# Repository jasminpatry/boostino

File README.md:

# BooSTIno
A Teensy 3.6-based logger and gauge for my 2014 Subaru STI.

Photo of current version:

Short [YouTube video](https://www.youtube.com/watch?v=nscQxxUsuL8) of older version, without faceplate or wideband support:

See [this thread on NASIOC](https://forums.nasioc.com/forums/showthread.php?t=2896098) for more info.

# Compilation

This project is built as an Arduino sketch. I used Arduino 1.8.8, but later versions will likely work too. You will also need the Teensyduino add-on
(https://www.pjrc.com/teensy/td_download.html), and the following libraries:

* My fork of ILI9341_t3: https://github.com/jasminpatry/ILI9341_t3
* My fork of Adafruit_GFX: https://github.com/jasminpatry/Adafruit-GFX-Library
* font_Exo-BoldItalic: https://github.com/FrankBoesing/fonts/tree/master/ofl/exo

# Hardware

This project was built using the following hardware:

* [Teensy 3.6](https://www.pjrc.com/store/teensy36.html)
* MC33660 K-line serial interface chip, SOP-8 package ([datasheet](https://www.nxp.com/docs/en/data-sheet/MC33660.pdf)); I purchased mine from [eBay](https://www.ebay.com/itm/10PCS-MC33660-MC33660EF-SOP-8/292559702234)
* Custom PCB fabricated using the files in the [KiCad/boostino.gerber](KiCad/boostino.gerber) directory (I used [BasicPCB](https://www.basicpcb.com/)'s ValueSpec option, which in 2020 cost me about $30 for 3 boards).
* [HiLetgo ILI9341 2.8" SPI TFT LCD Display Touch Panel 240X320 with PCB 5V/3.3V STM32](https://www.amazon.com/gp/product/B073R7BH1B/)
* [OBD-2 cable](https://www.amazon.com/gp/product/B01ETRINYO/) &mdash; the switch and DB9 connector in the linked cable aren't necessary (I snipped them off), but the DB9 connector was useful when prototyping.
* [Innovate Motorsports (3877) LC-2 Digital Wideband Lambda Controller Kit with Bosch LSU 4.9 O2 Sensor](https://www.amazon.com/Innovate-Motorsports-Digital-Wideband-Controller/dp/B00FFTAJPC/) (optional; only necessary for AFR display and logging)
* [Molex Micro-Fit 3.0 plug](https://www.amazon.com/gp/product/B078Q798L9/) for connecting to the LC-2 serial output (optional; only necessary for AFR display and logging)
* [Elcoho 10 Pieces Plastic Waterproof Boxes Junction Case Compatible with Electronic Project 3.94 × 2.36 × 0.98 Inches, Black](https://www.amazon.com/gp/product/B07G8S6XLV/)
* For the faceplate, I had [faceplate.eps](faceplate.eps) laser-cut by https://www.ponoko.com/ using:
    * Acrylic - Two Color - Brushed Silver on Black
    * 0.059 inches thick
    * P1 - 7.126 inches long x 7.126 inches wide
* Miscellaneous cables, headers, resistors, capacitors, diodes, wires, screws & nuts, etc.

# Tactrix Version

A previous version of this project used the [Tactrix OpenPort 2.0](https://www.tactrix.com/index.php?option=com_virtuemart&page=shop.product_details&product_id=17&vmcchk=1&Itemid=53&redirected=1&Itemid=53) to communicate with the ECU. That version is available in the [Tactrix](../../tree/Tactrix/) branch.

# Donate

If this project proves useful to you, please consider making a donation!

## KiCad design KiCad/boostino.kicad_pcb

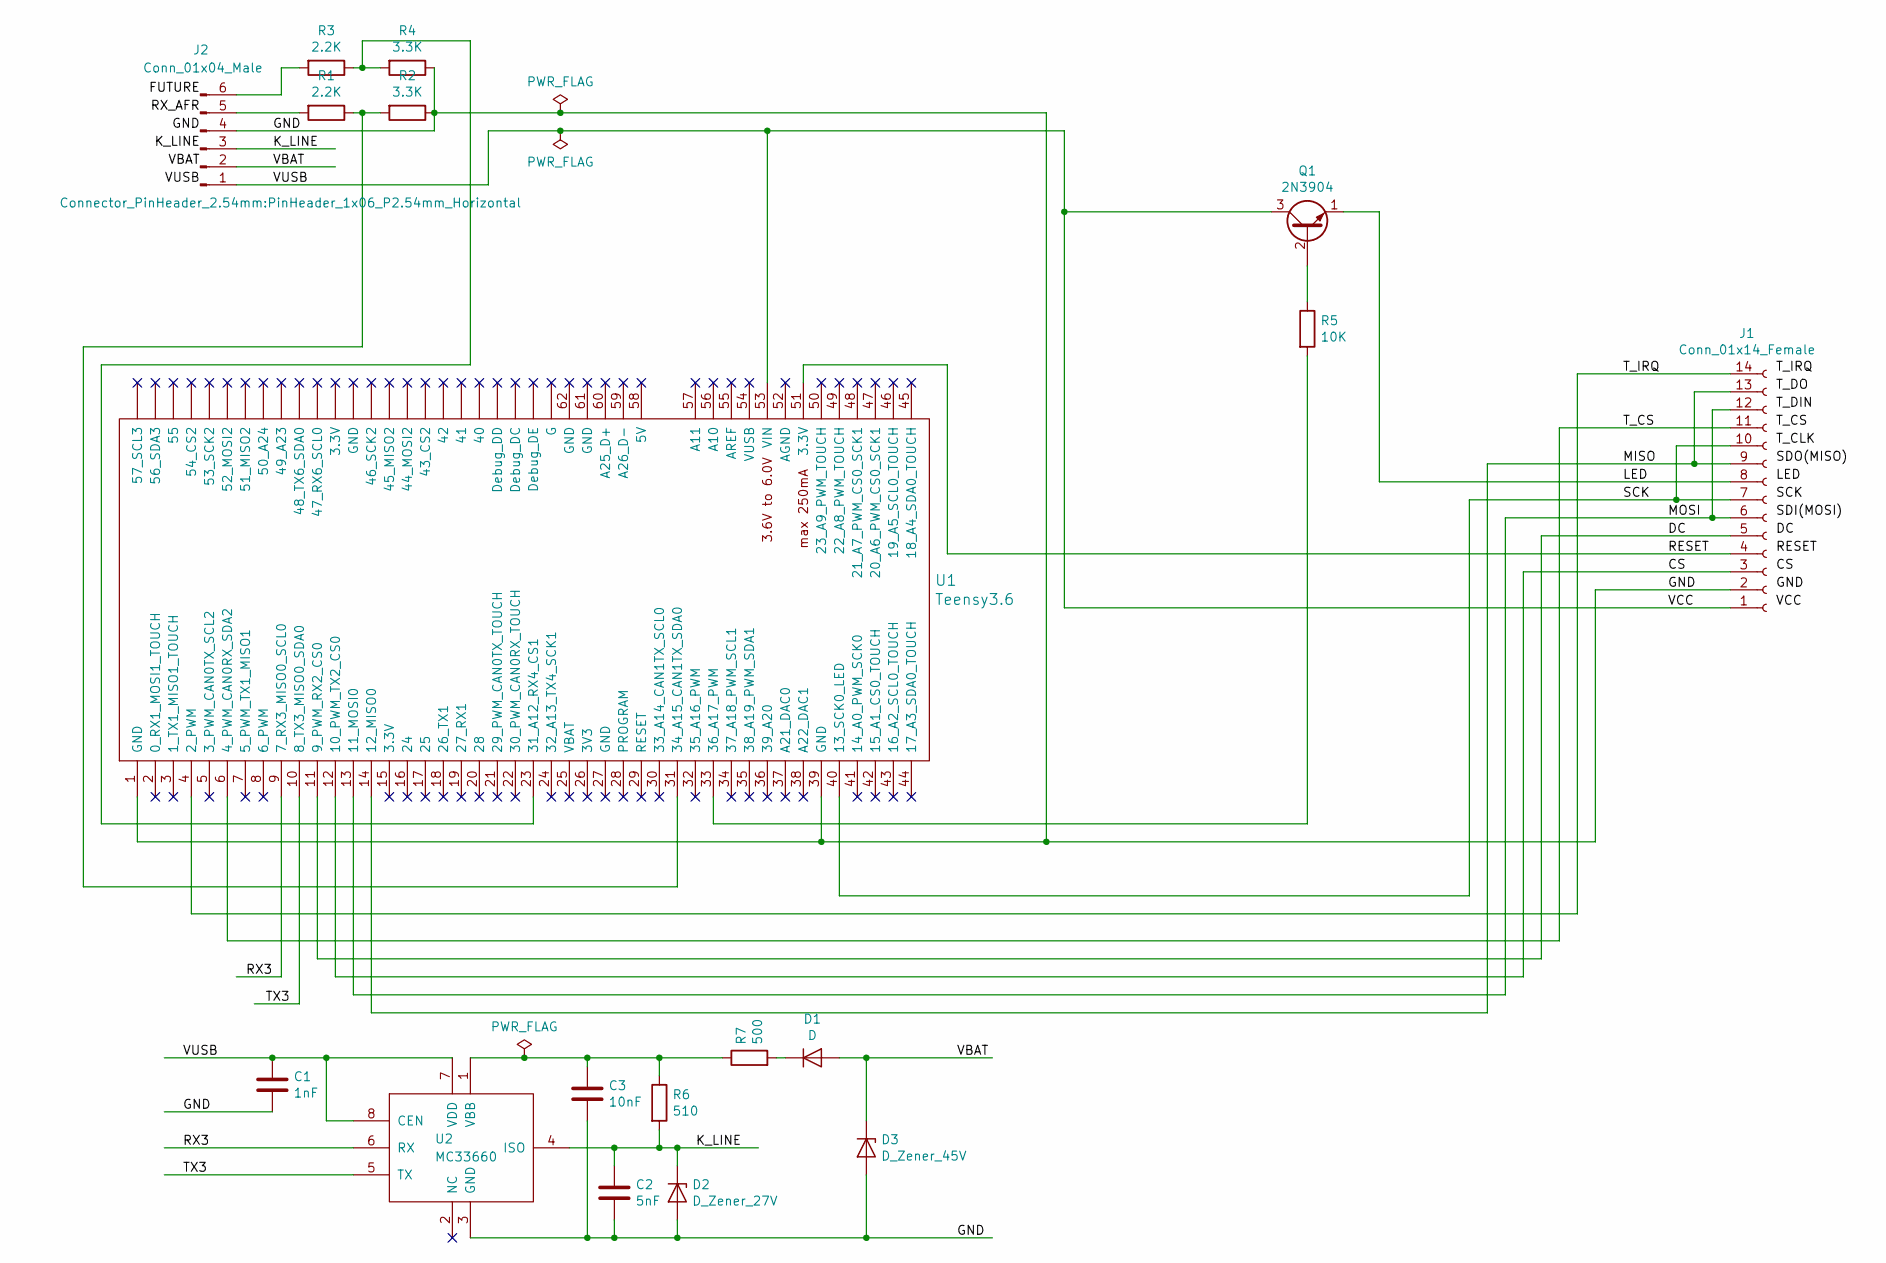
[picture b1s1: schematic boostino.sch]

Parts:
C1: 1nF; C_1206_3216Metric_Pad1.42x1.75mm_HandSolder
C2: 5nF; C_1206_3216Metric_Pad1.42x1.75mm_HandSolder
C3: 10nF; C_1206_3216Metric_Pad1.42x1.75mm_HandSolder
D1: D; D_A-405_P10.16mm_Horizontal
D2: D_Zener_27V; D_MiniMELF_Handsoldering
D3: D_Zener_45V; D_MiniMELF_Handsoldering
J1: Conn_01x14_Female; PinSocket_1x14_P2.54mm_Vertical
J2: Conn_01x04_Male; PinHeader_1x06_P2.54mm_Horizontal
Q1: 2N3904; TO-92_HandSolder
R1, R3: 2.2K; R_0805_2012Metric_Pad1.15x1.40mm_HandSolder
R2, R4: 3.3K; R_0805_2012Metric_Pad1.15x1.40mm_HandSolder
R5: 10K; R_0805_2012Metric_Pad1.15x1.40mm_HandSolder
R6: 510; R_0805_2012Metric_Pad1.15x1.40mm_HandSolder
R7: 500; R_0805_2012Metric_Pad1.15x1.40mm_HandSolder
U1: Teensy3.6; Teensy35_36
U2: MC33660; SOIC-8_3.9x4.9mm_P1.27mm

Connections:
/CS: J1.3, U1.12 (10_PWM_TX2_CS0)
/DC: J1.5, U1.11 (9_PWM_RX2_CS0)
/GND: C1.1, C2.1, C3.1, D2.2 (A), D3.2 (A), J1.2, J2.4, R2.1, R4.1, U1.1 (GND), U1.39 (GND), U2.3 (GND)
/K_LINE: C2.2, D2.1 (K), J2.3, R6.2, U2.4 (ISO)
/LED: J1.8, Q1.1 (E)
/MISO: J1.9, J1.13, U1.14 (12_MISO0)
/MOSI: J1.6, J1.12, U1.13 (11_MOSI0)
/RESET: J1.4, U1.51 (3.3V)
/RX3: U1.9 (7_RX3_MISO0_SCL0), U2.6 (RX)
/SCK: J1.7, J1.10, U1.40 (13_SCK0_LED)
/TX3: U1.10 (8_TX3_MISO0_SDA0), U2.5 (TX)
/T_CS: J1.11, U1.6 (4_PWM_CAN0RX_SDA2)
/T_IRQ: J1.14, U1.4 (2_PWM)
/VBAT: D1.2 (A), D3.1 (K), J2.2
/VCC: C1.2, J1.1, J2.1, Q1.3 (C), U1.53 (VIN), U2.7 (VDD), U2.8 (CEN)
unnamed: C3.2, R6.1, R7.1, U2.1 (VBB)
unnamed: D1.1 (K), R7.2
unnamed: J2.5, R1.2
unnamed: J2.6, R3.2
unnamed: Q1.2 (B), R5.1
unnamed: R1.1, R2.2, U1.31 (34_A15_CAN1TX_SDA0)
unnamed: R3.1, R4.2, U1.23 (31_A12_RX4_CS1)
unnamed: R5.2, U1.33 (36_A17_PWM)

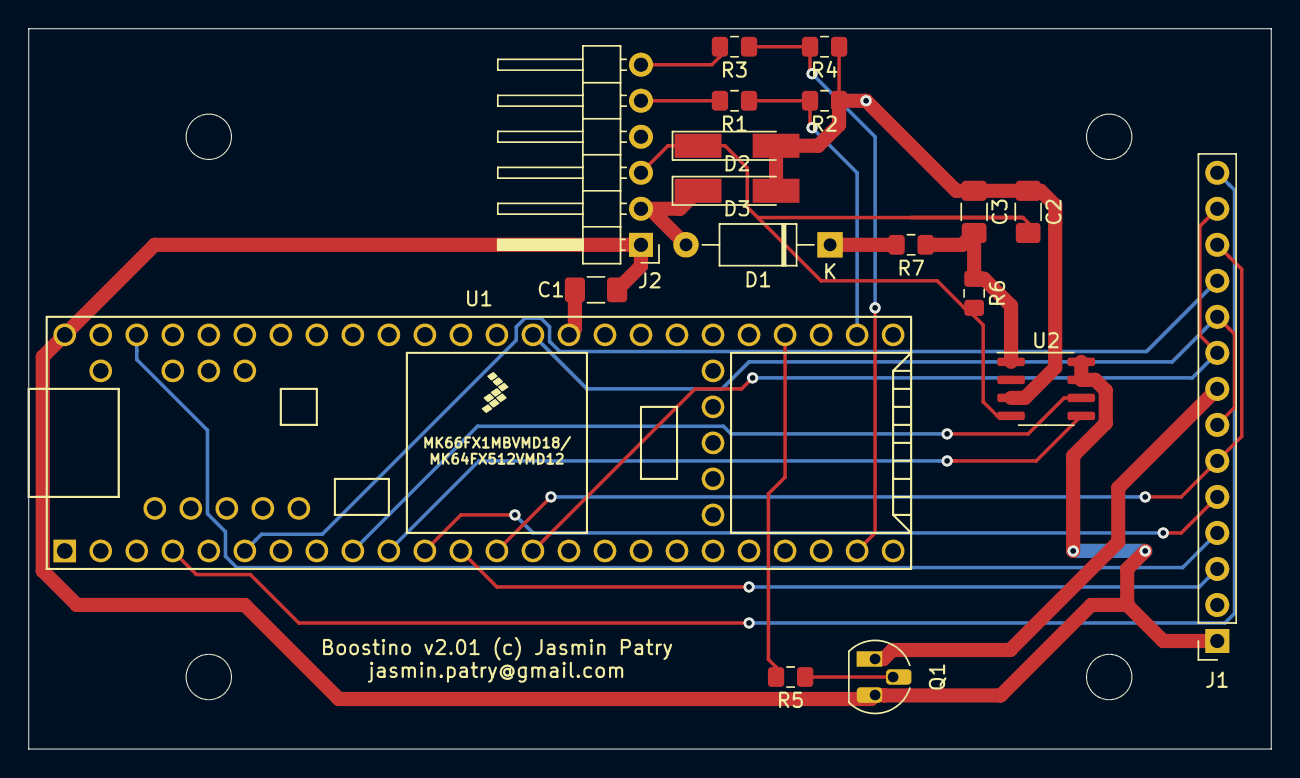
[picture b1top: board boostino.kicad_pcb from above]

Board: 2 copper layers, 87.6 x 50.8 mm, 18 parts (0 on the bottom side), 23 nets.

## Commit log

2019-02-03 Initial commit (copy of Teensy USBHost_t36 SerialTest example).
2019-02-03 Strip out extraneous stuff
2019-02-04 Initial Tactrix framework
2019-02-04 Implement preamble of init sequence
2019-02-04 SSM Init WIP
2019-02-04 SSM init complete
2019-02-04 Fixes
2019-02-04 Reworked message handling WIP
    For handling multiple messages per transfer.
    Completely untested!
2019-02-06 Completed revised message handling
2019-02-06 Init tweaks
2019-02-06 Add TraceHex
2019-02-09 Add address read request, untested
2019-02-09 Read request tested offline
2019-02-09 Add handling of read request replies (untested)
2019-02-09 Add polling code (untested)
2019-02-09 Fix assert
2019-02-09 Polling tested and working
2019-02-09 Initial OLED display support
2019-02-09 Added basic gauge display
2019-02-10 Add coolant temp
2019-02-10 Fix checksum calc; reformat display
2019-02-10 Add DisplayStatus
2019-02-10 Add Load, RPM, IAT
2019-02-10 Add SD init, cleanup, timed warning displays (untested)
2019-02-10 Add throttle pct and convert some params to 1-byte versions.
2019-02-10 Add circular log history buffer, and fix nasty lurking bug.
2019-02-11 Added logging to SD card on warning (untested)
2019-02-11 Bug fixes
2019-02-11 Add splash screen
2019-02-12 Comments
2019-02-17 Fix missing comma in log output
2019-02-18 Hacked to work with ILI9341 TFT display
2019-02-22 Add mockup.psd
2019-02-22 More hacking with offscreen canvas
2019-02-23 Tweaks to layout, exported background & foreground.
2019-02-24 Gauge drawing test
2019-02-25 Gauge animation test
2019-02-25 Draw to screen using differential update
2019-02-26 Display actual data (untested in vehicle)
2019-03-03 Restart polling after 10 seconds; test to try to fix polling errors.
2019-03-03 Try to fix handling of reply timeouts and uncrecognized messages
2019-03-03 Add touchscreen support
2019-03-04 Add IAM alert
2019-03-09 Add antialiased line drawing
2019-03-19 Added delays during startup & connection
    Attempt to fix Tactrix freeze-ups during boot, not 100% successful.
2019-03-19 Double initial delay and remove other delays (untested)
    Also use strPixelLen on canvas now that's it's in the Adafruit_GFX class.
2019-03-23 Remove delay; not necessary when Tactrix not set up to log.
2019-04-17 Add pull logs
    - Also made headers match the RomRaider ones for use in Virtual Dyno
2019-04-17 Log pulls and knock to same file
2019-04-18 Add IPW and IDC params
2019-04-28 Add PARAM_Afr1 for Air/Fuel Ratio #1
2019-05-14 More detailed comments about att/PassThruWriteMsgs
2019-05-26 Add LTV param data as comments
2019-06-19 Filter out low-load, low-intensity knock
2019-06-19 Always fully update one scanline to recover in case of display corruption.
2019-07-03 Fix FBKC min when resetting using touch.
2019-07-05 Cleanup
2019-07-09 Analog test code
2019-07-10 Add separate AFR and MPH labels; untested
2019-07-19 Add wideband AFR, wip
2019-07-19 Allow toggling between AFR & MPH
2019-07-26 Calibrated AFR and added filter to display
2019-08-27 MAF & AFR logging for MAF scaling, untested.
2019-08-28 Use 2-byte Final Fueling Base
2019-12-23 Update wideband calibration
2019-12-28 Turn off debug flags.
2019-12-28 Cleanup & comments.
2020-01-04 Rename
2020-01-05 Add license
2020-01-05 Add readme
2020-01-05 Add compilation info
2020-01-05 Added hardware info to readme; added faceplate.eps
2020-01-05 Fix type and link
2020-01-05 Fix another typo
2020-01-24 Remove voltage divider
    Innovate LC-2 now configured to output 0-3 V instead of 0-5.
2020-01-27 Use serial input for wideband AFR instead of analog.
    I was having problems maintaining accurate readings over the analog output of the Innovate Motorsports LC-2 wideband, so
    this change switches to using the serial output of the LC-2. The LC-2 outputs 0-5V RS-232 serial, so I'm using a voltage
    divider (2.2K & 3.3K) to step down to 0-3V, and using RXINV since TTL and RS-232 serial are inverted.
2020-01-27 Update readme with wideband links.
2020-01-30 Serial wideband display fixes and improvements.
2020-02-02 Add light switch detection and brightness adjustment
2020-02-09 Screen fading WIP
2020-02-16 Lerp in log space.
2020-02-18 Add touch controls for screen brightness.
    Remove LightSwitch detection since it always returns 1 when parking brake isn't on.
2020-09-06 Avoid clipping boost; save display brightness in EEPROM.
2020-09-26 Updated to work with MC33660 instead of Tactrix
2020-09-27 Add KiCad and Gerber files for PCB
2020-09-27 Add KiCad gitignore
2020-09-29 Updated PCB for MC33660. Still need to regenerate Gerber files.
2020-10-02 Generate Gerber files, bump PCB version to 2.0.
2020-10-08 Fully drain incoming message queue each update, cleanup
2020-10-08 Label diode in schematic
2020-10-08 Move K-Line to Serial3, and move touch CS pin from 8 to 6.
2020-10-08 Fix typo.
2020-10-08 Update PCB to use Serial3 for K-Line
2020-10-11 Turn off debug mode
2020-10-11 Update component values.
    Alternate values in brackets where applicable.
2020-10-11 Cleanup URL
2020-10-11 Add link to MC33660 datasheet
2020-10-13 Fix touch CS pin number
